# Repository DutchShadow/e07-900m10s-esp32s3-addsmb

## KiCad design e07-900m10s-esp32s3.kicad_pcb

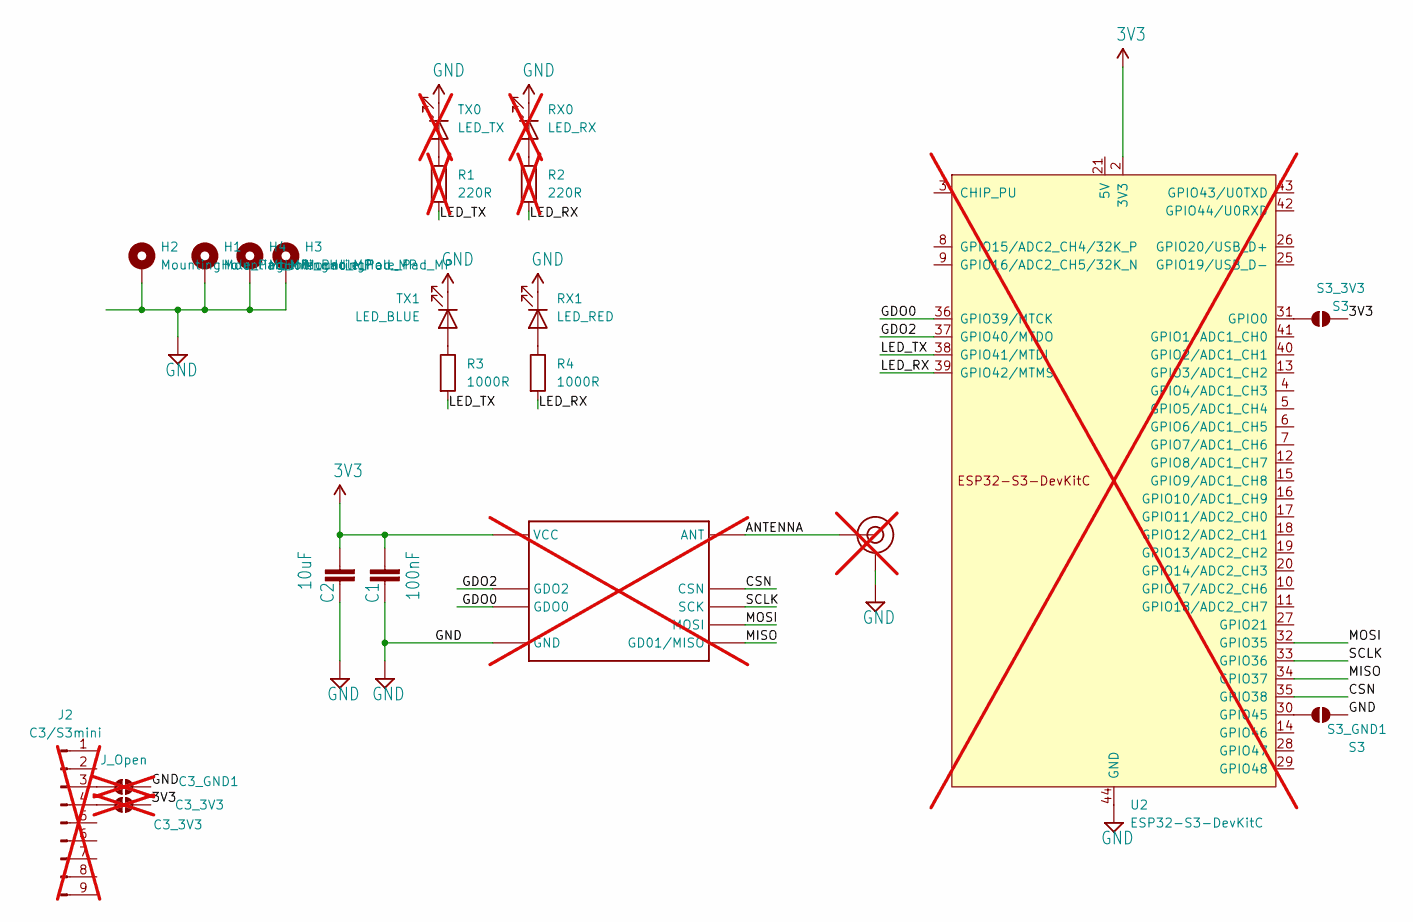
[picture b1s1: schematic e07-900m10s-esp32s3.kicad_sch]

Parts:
C1: 100nF; C_1210_3225Metric_Pad1.33x2.70mm_HandSolder; MPN C24497
C2: 10uF; C_1210_3225Metric_Pad1.33x2.70mm_HandSolder; MPN C13585
C3_3V3: C3_3V3; SolderJumper-2_P1.3mm_Open_TrianglePad1.0x1.5mm; not fitted
C3_GND1: J_Open; SolderJumper-2_P1.3mm_Open_TrianglePad1.0x1.5mm; not fitted
H1, H2, H3, H4: MountingHole_Pad_MP; MountingHole_2.5mm_Pad_Via
J2: C3/S3mini; PinSocket_1x09_P2.54mm_Vertical; not fitted
J$1: ANTENNASMA; SMA_PAD; not fitted
R1, R2: 220R; R_Axial_DIN0411_L9.9mm_D3.6mm_P12.70mm_Horizontal; not fitted
R3, R4: 1000R; R_1206_3216Metric_Pad1.30x1.75mm_HandSolder
RX0: LED_RX; LED_D4.0mm; not fitted
RX1: LED_RED; LED_0805_2012Metric; MPN C84256
S3_3V3, S3_GND1: S3; SolderJumper-2_P1.3mm_Open_TrianglePad1.0x1.5mm
TX0: LED_TX; LED_D4.0mm; not fitted
TX1: LED_BLUE; LED_0805_2012Metric; MPN C2297
U1: E07-900M10S; not fitted
U2: ESP32-S3-DevKitC; not fitted

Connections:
3V3: C1.2, C2.2, C3_3V3.2 (B), S3_3V3.2 (B), U1.9 (VCC), U2.1 (3V3), U2.2 (3V3)
/ANTENNA: J$1.ANT0 (ANT), J$1.ANT1 (ANT), J$1.ANT2 (ANT), U1.21 (ANT)
/CSN: U1.19 (CSN), U2.35 (GPIO38)
/GDO0: U1.15 (GDO0), U2.36 (GPIO39/MTCK)
/GDO2: U1.14 (GDO2), U2.37 (GPIO40/MTDO)
/LED_RX: R2.2, R4.2, U2.39 (GPIO42/MTMS)
/LED_TX: R1.2, R3.2, U2.38 (GPIO41/MTDI)
/MISO: U1.16 (GD01/MISO), U2.34 (GPIO37)
/MOSI: U1.17 (MOSI), U2.32 (GPIO35)
/SCLK: U1.18 (SCK), U2.33 (GPIO36)
GND: C1.1, C2.1, C3_GND1.2 (B), H1.MP, H2.MP, H3.MP, H4.MP, J$1.GND3 (GND), J$1.GND4 (GND), J$1.GND5 (GND), J$1.GND6 (GND), RX0.1 (K), RX1.1 (K), S3_GND1.2 (B), TX0.1 (K), TX1.1 (K), U1.1 (GND), U1.2 (GND), U1.3 (GND), U1.4 (GND), U1.5 (GND), U1.11 (GND), U1.12 (GND), U1.20 (GND), U1.22 (GND), U2.22 (GND), U2.23 (GND), U2.24 (GND), U2.44 (GND)
unnamed: C3_3V3.1 (A), J2.4
unnamed: C3_GND1.1 (A), J2.3
unnamed: R2.1, RX0.2 (A)
unnamed: R4.1, RX1.2 (A)
unnamed: S3_3V3.1 (A), U2.31 (GPIO0)
unnamed: S3_GND1.1 (A), U2.30 (GPIO45)
unnamed: R1.1, TX0.2 (A)
unnamed: R3.1, TX1.2 (A)

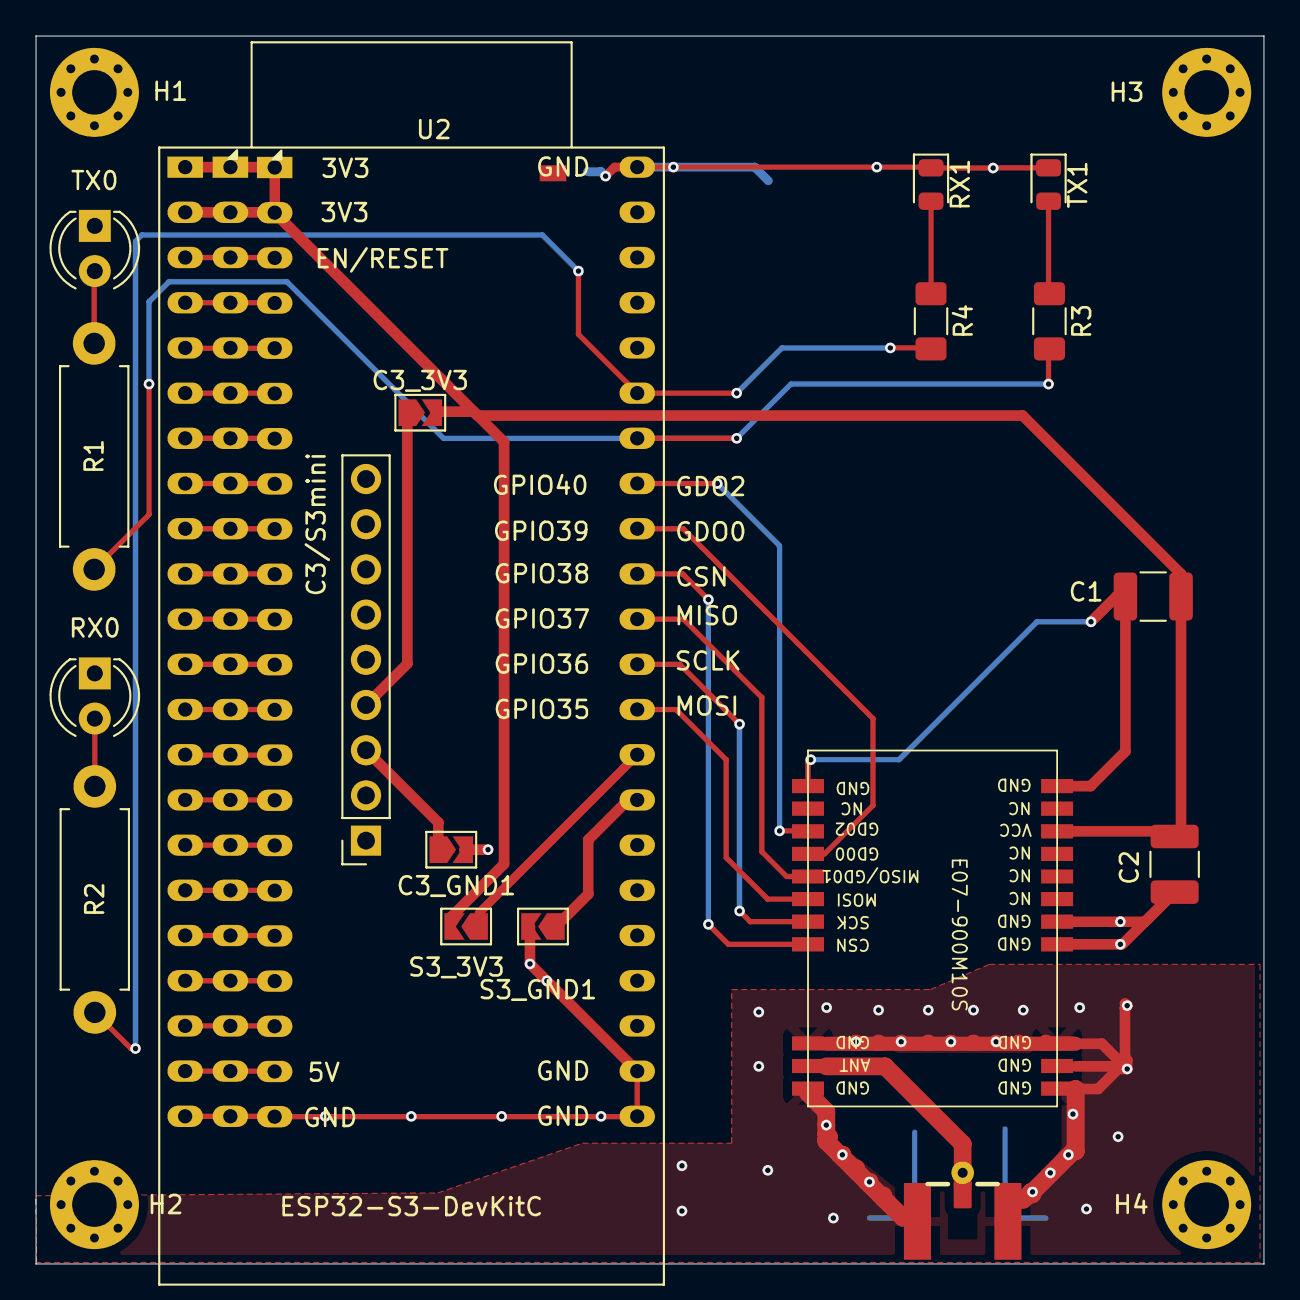
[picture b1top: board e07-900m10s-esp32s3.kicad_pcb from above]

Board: 2 copper layers, 69.0 x 69.0 mm, 22 parts (0 on the bottom side), 19 nets.

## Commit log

2024-09-12 New version for JLC production
    Header removed, PCB extended LED's switched for standard basic part and added MPN to components JLC solders.
